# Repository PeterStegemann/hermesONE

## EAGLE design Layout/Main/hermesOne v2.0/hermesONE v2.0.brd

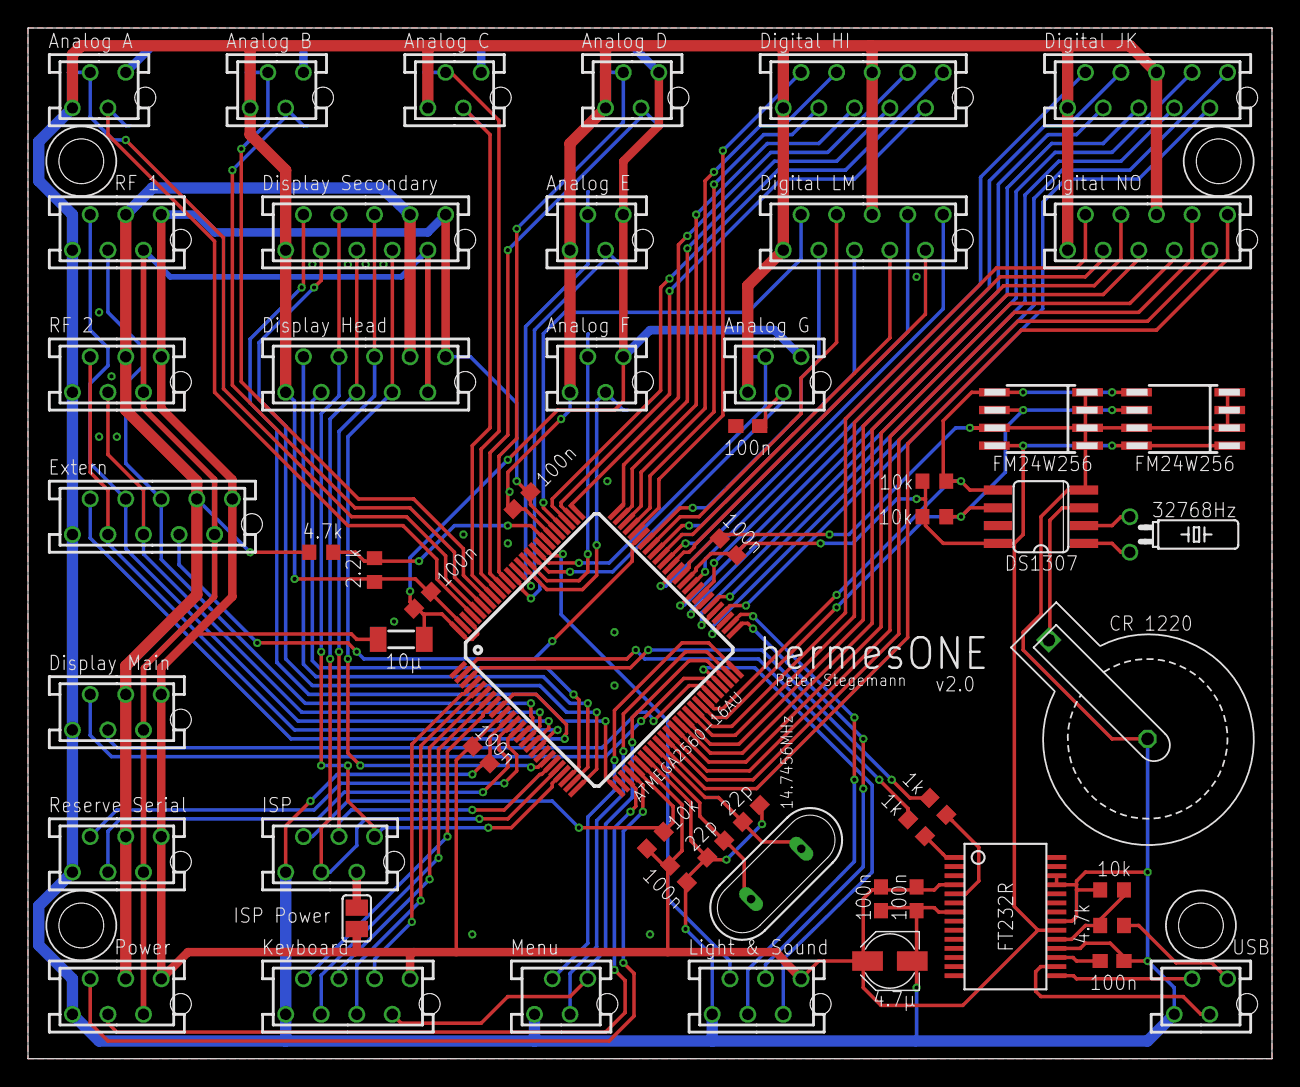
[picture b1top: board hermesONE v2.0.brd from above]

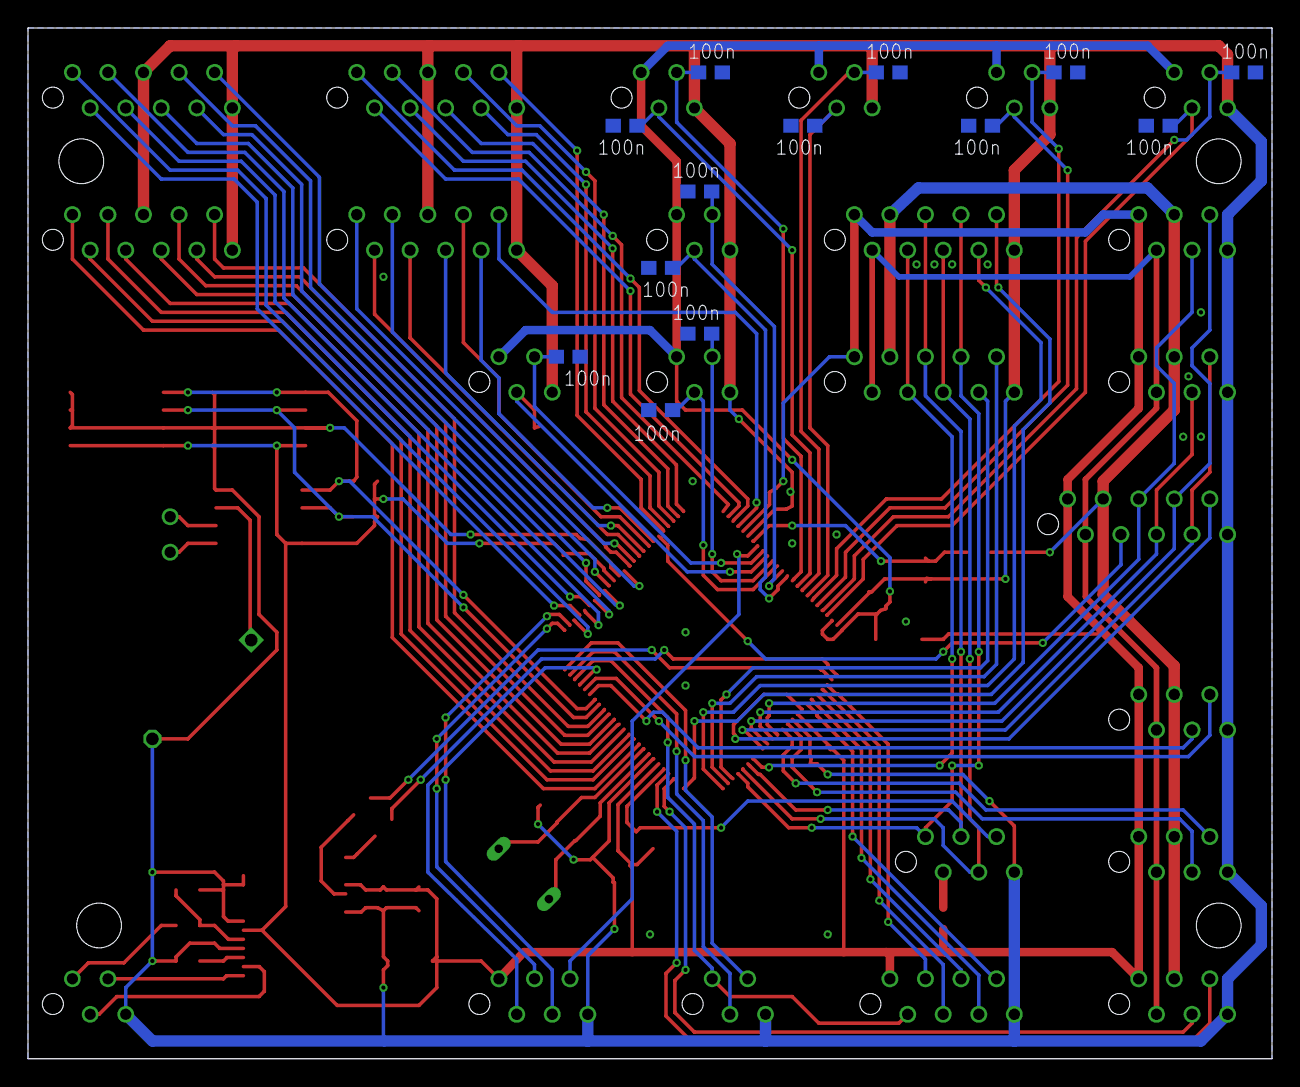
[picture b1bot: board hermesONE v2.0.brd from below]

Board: 2 copper layers, 88.9 x 73.7 mm, 68 parts (13 on the bottom side), 102 nets.

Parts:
C1, C2: 22p; C0603
C3, C4, C5, C6, C7, C8, C9, C10, C12, C13, C14, C15, C16, C17, C18, C19, C20, C21, C22, C23, C24, C25: 100n; C0603
C11: 4.7µ; PANASONIC_B
G1: CR 1220; KZH12THM
IC1: ATMEGA2560-16AU; TQFP100
IC3: DS1307; SOIC-8
IC4, IC5: FM24W256; SO-08M
L1: 10µ; SM-1206
M1: Analog A; MT-4
M2: Analog B; MT-4
M3: Analog C; MT-4
M4: Analog D; MT-4
M5: Analog E; MT-4
M6: Analog F; MT-4
M7: Analog G; MT-4
M8: Digital HI; MT-10
M9: Digital JK; MT-10
M10: Digital LM; MT-10
M11: Digital NO; MT-10
M20: Power; MT-6
M21: ISP; MT-6
M23: USB; MT-4
M30: RF 1; MT-6
M31: RF 2; MT-6
M32: Extern; MT-10
M40: Display Head; MT-10
M41: Display Secondary; MT-10
M42: Display Main; MT-6
M43: Reserve Serial; MT-6
M50: Light & Sound; MT-6
M51: Menu; MT-4
M52: Keyboard; MT-8
Q1: 14.7456MHz; QS
Q2: 32768Hz; TC26H
R1, R2, R3, R7: 10k; R0603
R4: 2.2k; R0603
R5, R6: 4.7k; R0603
R8, R9: 1k; R0603
SJ1: ISP Power; SJ
U1: FT232R; SSOP28DB

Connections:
3V3: M20.2, M30.2, M31.2, M32.2, M40.2, M41.2, M42.2, M43.2
3V3OUT: C10.2, U1.17
/RESET: IC1.30, M21.5, R1.2
ANALOG_A1: C12.1, IC1.97, M1.2
ANALOG_A2: C13.1, IC1.96, M1.3
ANALOG_B1: C14.1, IC1.95, M2.2
ANALOG_B2: C15.1, IC1.94, M2.3
ANALOG_C1: C16.1, IC1.93, M3.2
ANALOG_C2: C17.1, IC1.92, M3.3
ANALOG_D1: C18.1, IC1.91, M4.2
ANALOG_D2: C19.1, IC1.90, M4.3
ANALOG_E1: C20.1, IC1.89, M5.2
ANALOG_E2: C21.1, IC1.88, M5.3
ANALOG_F1: C22.1, IC1.87, M6.2
ANALOG_F2: C23.1, IC1.86, M6.3
ANALOG_G1: C24.1, IC1.85, M7.2
ANALOG_G2: C25.1, IC1.84, M7.3
AVCC: C5.1, IC1.98, IC1.100, L1.2, M1.1, M2.1, M3.1, M4.1, M5.1, M6.1, M7.1
BATTERY: M20.3, M30.3, M31.3, M32.3, M40.3, M41.3, M42.3, M43.3, R5.2
BATTERY_CONTROL: IC1.82, R4.1, R5.1
BUZZER: IC1.47, M50.2
D+: M23.3, U1.15
D-: M23.2, U1.16
DIGITAL_H1: IC1.78, M8.1
DIGITAL_H2: IC1.77, M8.2
DIGITAL_H3: IC1.76, M8.3
DIGITAL_H4: IC1.75, M8.4
DIGITAL_I1: IC1.74, M8.6
DIGITAL_I2: IC1.73, M8.7
DIGITAL_I3: IC1.72, M8.8
DIGITAL_I4: IC1.71, M8.9
DIGITAL_J1: IC1.53, M9.1
DIGITAL_J2: IC1.54, M9.2
DIGITAL_J3: IC1.55, M9.3
DIGITAL_J4: IC1.56, M9.4
DIGITAL_K1: IC1.57, M9.6
DIGITAL_K2: IC1.58, M9.7
DIGITAL_K3: IC1.59, M9.8
DIGITAL_K4: IC1.60, M9.9
DIGITAL_L1: IC1.63, M10.1
DIGITAL_L2: IC1.64, M10.2
DIGITAL_L3: IC1.65, M10.3
DIGITAL_L4: IC1.66, M10.4
DIGITAL_M1: IC1.67, M10.6
DIGITAL_M2: IC1.68, M10.7
DIGITAL_M3: IC1.69, M10.8
DIGITAL_M4: IC1.79, M10.9
DIGITAL_N1: IC1.35, M11.1
DIGITAL_N2: IC1.36, M11.2
DIGITAL_N3: IC1.37, M11.3
DIGITAL_N4: IC1.38, M11.4
DIGITAL_O1: IC1.39, M11.6
DIGITAL_O2: IC1.40, M11.7
DIGITAL_O3: IC1.41, M11.8
DIGITAL_O4: IC1.42, M11.9
DISPLAY_HEAD_LIGHT: IC1.24, M40.9
DISPLAY_HEAD_SELECT: IC1.23, M40.8
DISPLAY_RX: IC1.45, M42.4
DISPLAY_SECONDARY_LIGHT: IC1.26, M41.9
DISPLAY_SECONDARY_SELECT: IC1.25, M41.8
DISPLAY_TX: IC1.46, M42.5
GND: C1.2, C2.2, C3.1, C4.1, C5.2, C6.2, C7.2, C8.2, C9.2, C10.1, C11.-, C12.2, C13.2, C14.2, C15.2, C16.2, C17.2, C18.2, C19.2, C20.2, C21.2, C22.2, C23.2, C24.2, C25.2, G1.-, IC1.11, IC1.32, IC1.62, IC1.81, IC1.99, IC3.4, IC4.1, IC4.2, IC4.3, IC4.4, IC4.7, IC5.2, IC5.3, IC5.4, IC5.7, M1.4, M2.4, M3.4, M4.4, M5.4, M6.4, M7.4, M8.5, M8.10, M9.5, M9.10, M10.5, M10.10, M11.5, M11.10, M20.6, M21.6, M23.4, M30.6, M31.6, M32.10, M40.10, M41.10, M42.6, M43.6, M50.6, M51.4, M52.8, R4.2, R7.2, U1.7, U1.18, U1.21, U1.25, U1.26
ISP_VCC: M21.2, SJ1.1
KEYBOARD_0: IC1.4, M52.3
KEYBOARD_1: IC1.5, M52.4
KEYBOARD_2: IC1.6, M52.5
KEYBOARD_3: IC1.7, M52.6
KEYBOARD_4: IC1.8, M52.7
LED_GREEN: IC1.52, M50.4
LED_RED: IC1.51, M50.3
LIGHT_SENSOR: IC1.83, M50.5
MENU_BUTTON: IC1.48, M51.1, M52.2
MENU_ROTARY_A: IC1.49, M51.2
MENU_ROTARY_B: IC1.50, M51.3
MISO/SPI_RESET: IC1.22, M21.1, M40.7, M41.7
MOSI/SPI_DATA: IC1.21, M21.4, M40.6, M41.6
POWER_BUTTON: IC1.28, M20.4
POWER_ON: IC1.29, M20.5
PPM_INPUT: IC1.9, M32.9
PPM_OUTPUT_1: IC1.16, M30.5, M32.7
PPM_OUTPUT_2: IC1.17, M31.5, M32.8
RESERVE_RX: IC1.12, M43.4
RESERVE_TX: IC1.13, M43.5
RF_ENABLE_1: IC1.14, M30.4, M32.5
RF_ENABLE_2: IC1.15, M31.4, M32.6
RXD: R9.1, U1.5
SCK/SPI_CLOCK: IC1.20, M21.3, M40.5, M41.5
SPI_DC: IC1.19, M40.4, M41.4
TRAINER_ACTIVE: IC1.70, M32.4
TWI_SCL: IC1.43, IC3.6, IC4.6, IC5.6, R2.2
TWI_SDA: IC1.44, IC3.5, IC4.5, IC5.5, R3.2
TXD: R8.1, U1.1
USB_RESET: R6.2, R7.1, U1.19
USB_RX: IC1.2, R8.2
USB_TX: IC1.3, R9.2
USB_VCC: M23.1, R6.1
VBAT: G1.+, IC3.3
VCC: C3.2, C4.2, C6.1, C7.1, C8.1, C9.1, C11.+, IC1.10, IC1.31, IC1.61, IC1.80, IC3.8, IC4.8, IC5.1, IC5.8, L1.1, M20.1, M30.1, M31.1, M32.1, M40.1, M41.1, M42.1, M43.1, M50.1, M52.1, R1.1, R2.1, R3.1, SJ1.2, U1.4, U1.20
X1: IC3.1, Q2.2
X2: IC3.2, Q2.1
XTAL1: C1.1, IC1.34, Q1.1
XTAL2: C2.1, IC1.33, Q1.2
